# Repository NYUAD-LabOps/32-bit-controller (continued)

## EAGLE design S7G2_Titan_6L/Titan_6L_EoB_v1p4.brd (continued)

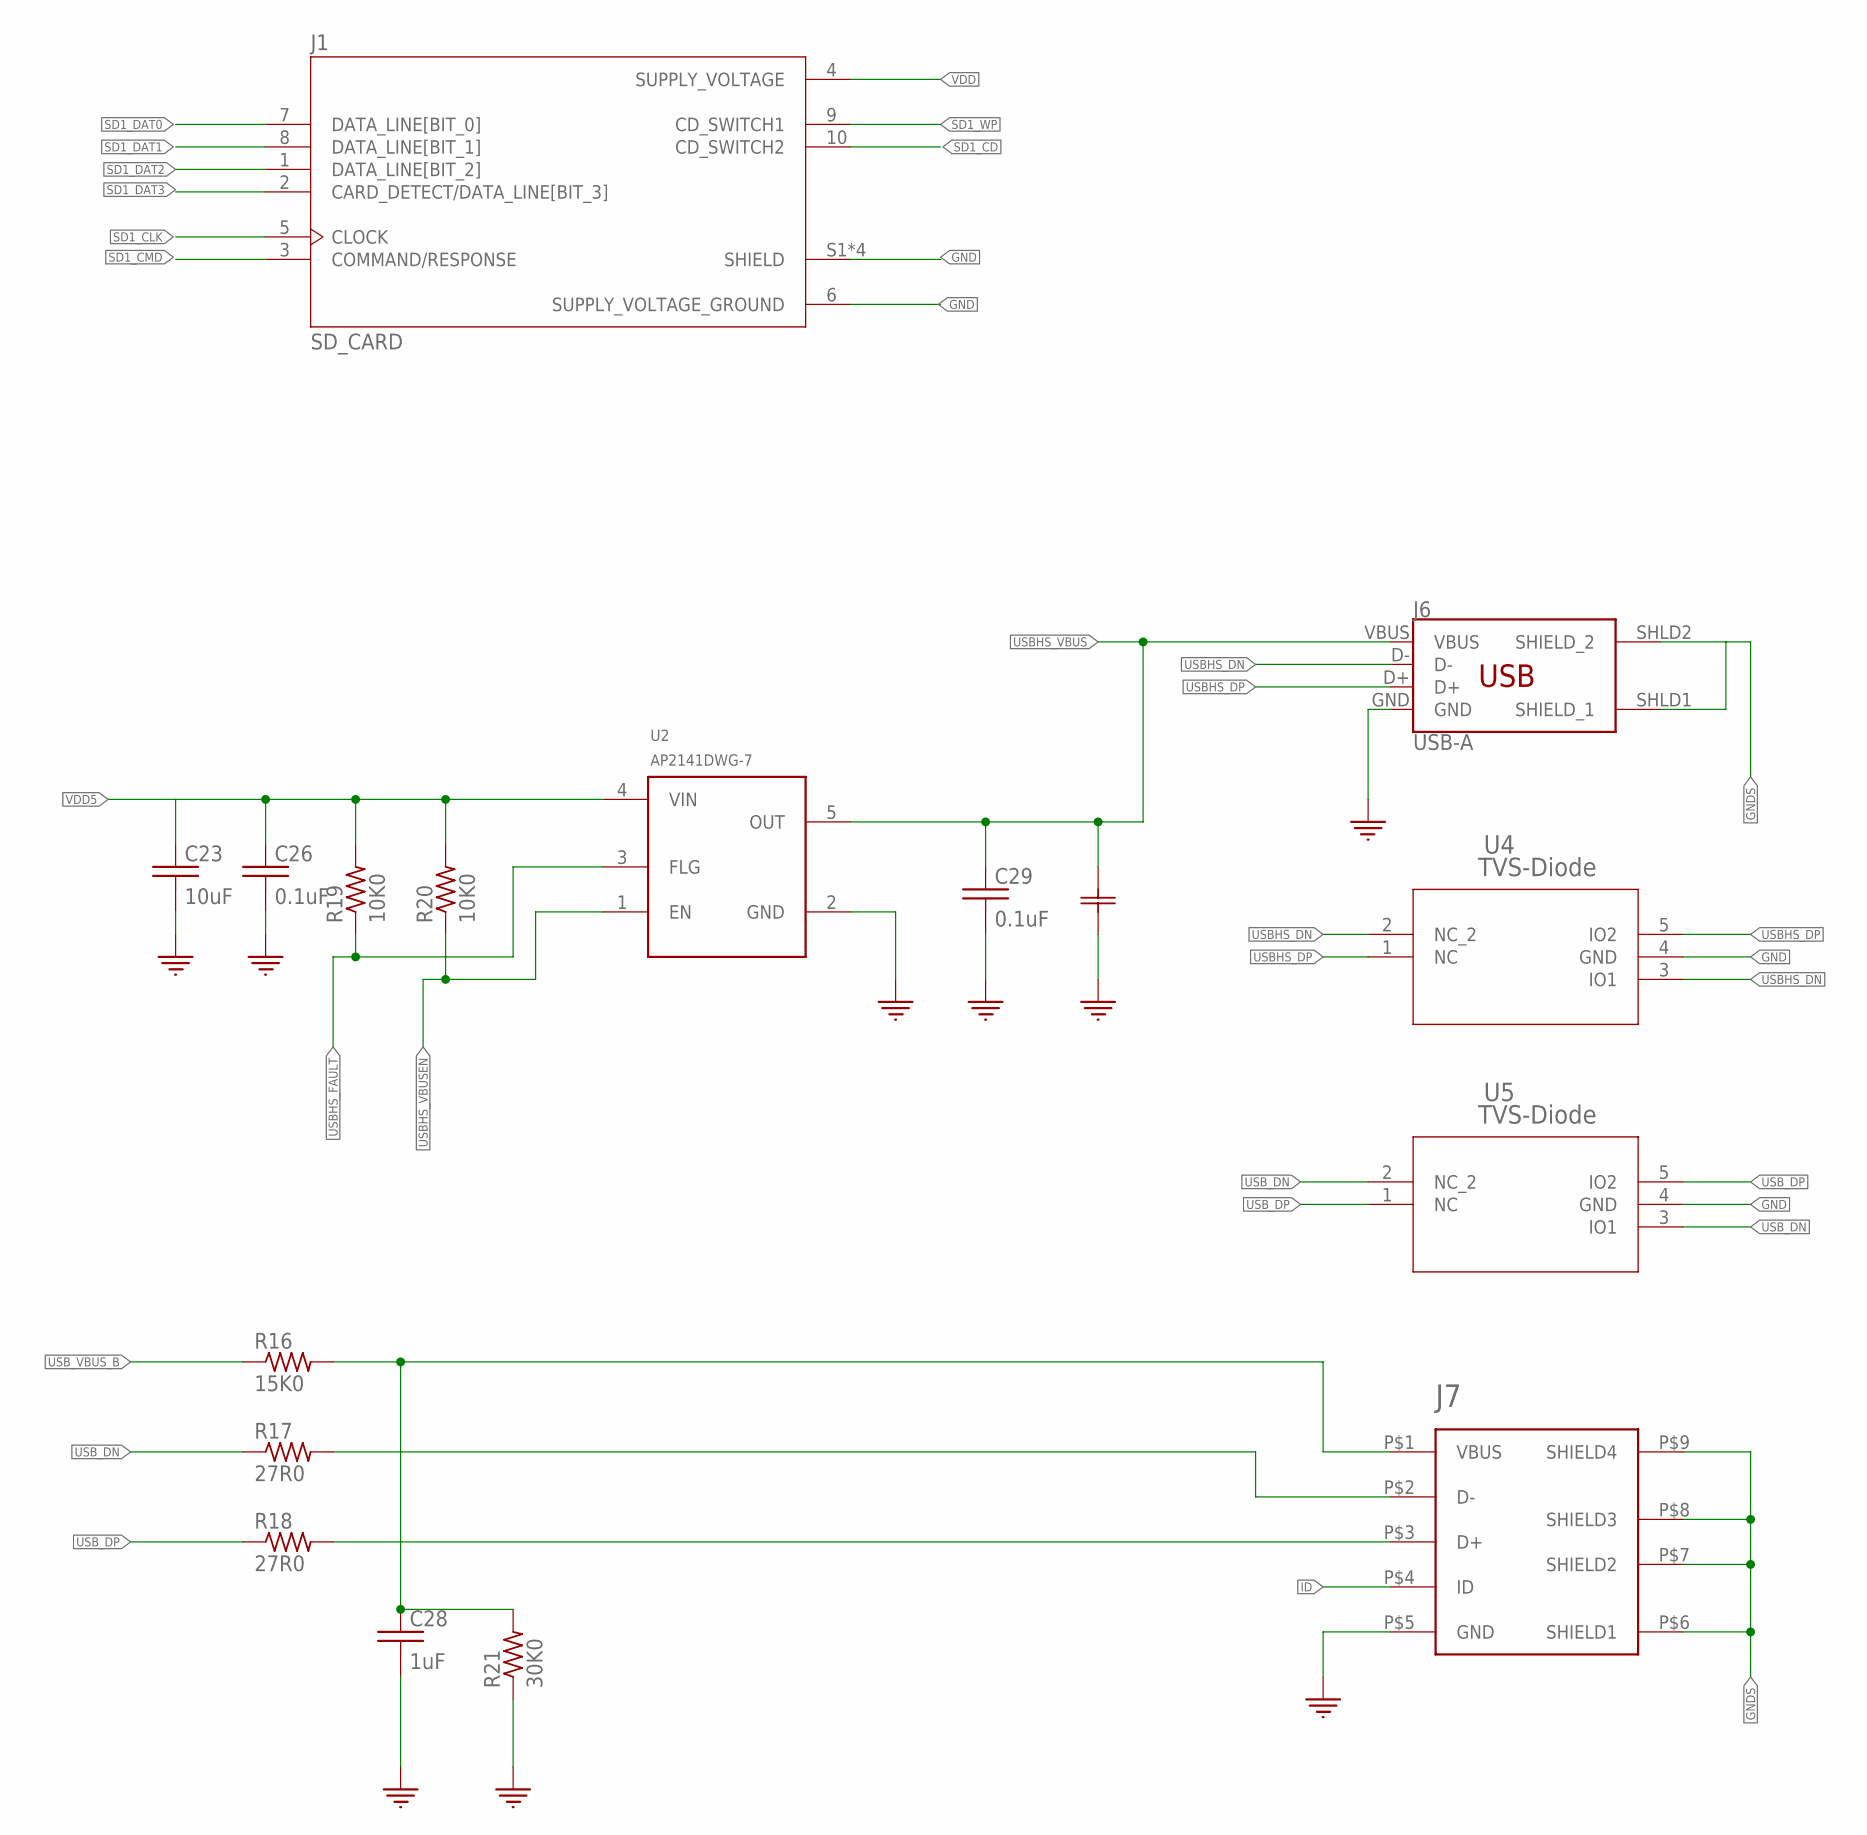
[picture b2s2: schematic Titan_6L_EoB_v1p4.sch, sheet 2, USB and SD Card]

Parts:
C1: TLJT107M010R0900CAP_1210TJLJ_3P5X2P8_DIO-M; CAP_1210TJLJ_3P5X2P8_DIO-M
C23: 10uF; 0402
C26, C29: 0.1uF; 0402
C28: 1uF; 0402
J1: SD_CARD
J6: USB-A; USB_A_SMT
J7: USB-B-Micro; USB_MICRO-B
R16: 15K0; 0402
R17, R18: 27R0; 0402
R19, R20: 10K0; 0402
R21: 30K0; 0402
U2: AP2151DWG-7; SOT-23-5
U4, U5: TVS-Diode; DRL5

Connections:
D+: J7.P$3 (D+), R18.P$2 (2)
D-: J7.P$2 (D-), R17.P$2 (2)
GND: C1.2, C23.P$2 (2), C26.P$2 (2), C28.P$2 (2), C29.P$2 (2), J1.6 (SUPPLY_VOLTAGE_GROUND), J1.S1 (SHIELD), J1.S2 (SHIELD), J1.S3 (SHIELD), J1.S4 (SHIELD), J6.GND, J7.P$5 (GND), R21.P$1 (1), U2.2 (GND), U4.4 (GND), U5.4 (GND); also elsewhere on the board
GNDS: J6.SHLD1 (SHIELD_1), J6.SHLD2 (SHIELD_2), J7.P$6 (SHIELD1), J7.P$7 (SHIELD2), J7.P$8 (SHIELD3), J7.P$9 (SHIELD4); also elsewhere on the board
ID: J7.P$4 (ID)
SD1_CD: J1.10 (CD_SWITCH2); also elsewhere on the board
SD1_CLK: J1.5 (CLOCK); also elsewhere on the board
SD1_CMD: J1.3 (COMMAND/RESPONSE); also elsewhere on the board
SD1_DAT0: J1.7 (DATA_LINE[BIT_0]); also elsewhere on the board
SD1_DAT1: J1.8 (DATA_LINE[BIT_1]); also elsewhere on the board
SD1_DAT2: J1.1 (DATA_LINE[BIT_2]); also elsewhere on the board
SD1_DAT3: J1.2 (CARD_DETECT/DATA_LINE[BIT_3]); also elsewhere on the board
SD1_WP: J1.9 (CD_SWITCH1); also elsewhere on the board
USBHS_DN: J6.D-, U4.2 (NC_2), U4.3 (IO1); also elsewhere on the board
USBHS_DP: J6.D+, U4.1 (NC), U4.5 (IO2); also elsewhere on the board
USBHS_FAULT: R19.P$1 (1), U2.3 (FLG); also elsewhere on the board
USBHS_VBUS: C1.1, C29.P$1 (1), J6.VBUS, U2.5 (OUT); also elsewhere on the board
USBHS_VBUSEN: R20.P$1 (1), U2.1 (EN)
USB_DN: R17.P$1 (1), U5.2 (NC_2), U5.3 (IO1); also elsewhere on the board
USB_DP: R18.P$1 (1), U5.1 (NC), U5.5 (IO2); also elsewhere on the board
USB_VBUS_B: R16.P$1 (1); also elsewhere on the board
VBUS: C28.P$1 (1), J7.P$1 (VBUS), R16.P$2 (2), R21.P$2 (2)
VDD: J1.4 (SUPPLY_VOLTAGE); also elsewhere on the board
VDD5: C23.P$1 (1), C26.P$1 (1), R19.P$2 (2), R20.P$2 (2), U2.4 (VIN); also elsewhere on the board

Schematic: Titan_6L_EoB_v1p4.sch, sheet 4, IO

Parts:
J8, J9, J11, J23, J25, J26, J27, J28, J29, J30, J31, J32, J33, J34: CONN_530470210_PICOBLADE_X_2; CON_530470210_MOL
J10, J13, J14, J15, J16, J17, J18, J19, J20, J21, J22, J24: CONN_530470410_PICOBLADE_X_4; CON_530470410_MOL
J12: 10-pos; 2X5
LED3, LED4, LED5, LED6, LED7, LED8, LED9, LED10, LED11, LED12, LED13, LED14, LED15, LED16: Green; 0805
R1, R2, R96, R97, R102, R103, R105, R106: 100K; 0402
R3, R12, R91, R93: 500R0; 0402
R4, R8, R61, R67, R70, R73, R78, R81, R84, R88: 2.2K; 0402
R6, R9, R11, R27, R62, R68, R71, R76, R79, R82, R85, R89, R92, R95: 470R0; 0402
R7, R10, R63, R69, R72, R77, R80, R83, R86, R90: 10K0; 0402
R28, R29, R30, R31, R32, R33, R34, R35, R36, R37, R38, R39, R40, R41, R42, R43, R44, R45, R46, R47, R48, R49, R50, R51, R52, R53, R54, R55, R56, R57, R58, R59, R60, R64, R65, R66: 33R0; 0402
TH01, TH02, TH03, TH04, TH05, TH06, TH07, TH08: CONN_530470210_PICOBLADE_X_2; CON_530470210_MOL
U7, U8, U9, U10, U11, U12, U13, U14, U15, U16, U17, U18, U19, U20, U21, U22, U23, U24, U25, U26, U27, U28, U29, U30, U31, U32, U33, U34, U35, U36, U37, U38, U39, U40, U41, U42, U43, U44, U45, U46, U47, U48, U49, U50, U51, U52, U53, U54, U55, U56: NPN; SOT323

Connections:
ESTOP: R89.P$2 (2), R90.P$2 (2), U53.2 (E(1)); also elsewhere on the board
GND: J8.1, J9.1, J10.1, J13.1, J14.1, J15.1, J16.1, J17.1, J18.1, J19.1, J20.1, J21.1, J22.1, J23.1, J24.1, J25.1, J26.1, J27.1, J28.1, J29.1, J30.1, J31.1, LED3.2 (C), LED4.2 (C), LED6.2 (C), LED7.2 (C), LED8.2 (C), LED9.2 (C), LED10.2 (C), LED11.2 (C), LED12.2 (C), LED13.2 (C), R7.P$1 (1), R10.P$1 (1), R63.P$1 (1), R69.P$1 (1), R72.P$1 (1), R77.P$1 (1), R80.P$1 (1), R83.P$1 (1), R86.P$1 (1), R90.P$1 (1), TH01.1, TH02.1, TH03.1, TH04.1, TH05.1, TH06.1, TH07.1, TH08.1, U9.2 (E(1)), U10.2 (E(1)), U11.2 (E(1)), U12.2 (E(1)), U13.2 (E(1)), U14.2 (E(1)), U15.2 (E(1)), U16.2 (E(1)), U17.2 (E(1)), U18.2 (E(1)), U19.2 (E(1)), U20.2 (E(1)), U21.2 (E(1)), U22.2 (E(1)), U23.2 (E(1)), U24.2 (E(1)), U25.2 (E(1)), U26.2 (E(1)), U27.2 (E(1)), U28.2 (E(1)), U29.2 (E(1)), U30.2 (E(1)), U31.2 (E(1)), U32.2 (E(1)), U33.2 (E(1)), U34.2 (E(1)), U35.2 (E(1)), U36.2 (E(1)), U37.2 (E(1)), U38.2 (E(1)), U39.2 (E(1)), U40.2 (E(1)), U41.2 (E(1)), U42.2 (E(1)), U45.2 (E(1)), U46.2 (E(1)), U47.2 (E(1)), U54.2 (E(1)), U55.2 (E(1)), U56.2 (E(1)); also elsewhere on the board
LS_01: R6.P$2 (2), R7.P$2 (2), U7.2 (E(1)); also elsewhere on the board
LS_02: R9.P$2 (2), R10.P$2 (2), U8.2 (E(1)); also elsewhere on the board
LS_03: R62.P$2 (2), R63.P$2 (2), U43.2 (E(1)); also elsewhere on the board
LS_04: R68.P$2 (2), R69.P$2 (2), U44.2 (E(1)); also elsewhere on the board
LS_05: R71.P$2 (2), R72.P$2 (2), U48.2 (E(1)); also elsewhere on the board
LS_06: R76.P$2 (2), R77.P$2 (2), U49.2 (E(1)); also elsewhere on the board
LS_07: R79.P$2 (2), R80.P$2 (2), U50.2 (E(1)); also elsewhere on the board
LS_08: R82.P$2 (2), R83.P$2 (2), U51.2 (E(1)); also elsewhere on the board
LS_09: R85.P$2 (2), R86.P$2 (2), U52.2 (E(1)); also elsewhere on the board
LS_RET: J8.2, J9.2, J23.2, J25.2, J26.2, J27.2, J28.2, J29.2, J30.2, J31.2, R4.P$1 (1), R8.P$1 (1), R61.P$1 (1), R67.P$1 (1), R70.P$1 (1), R73.P$1 (1), R78.P$1 (1), R81.P$1 (1), R84.P$1 (1), R88.P$1 (1)
M1_DIR: R29.P$1 (1); also elsewhere on the board
M1_ENABLE: R30.P$1 (1); also elsewhere on the board
M1_STEP: R28.P$1 (1); also elsewhere on the board
M2_DIR: R32.P$1 (1); also elsewhere on the board
M2_ENABLE: R33.P$1 (1); also elsewhere on the board
M2_STEP: R31.P$1 (1); also elsewhere on the board
M3_DIR: R35.P$1 (1); also elsewhere on the board
M3_ENABLE: R36.P$1 (1); also elsewhere on the board
M3_STEP: R34.P$1 (1); also elsewhere on the board
M4_DIR: R38.P$1 (1); also elsewhere on the board
M4_ENABLE: R39.P$1 (1); also elsewhere on the board
M4_STEP: R37.P$1 (1); also elsewhere on the board
M5_DIR: R41.P$1 (1); also elsewhere on the board
M5_ENABLE: R42.P$1 (1); also elsewhere on the board
M5_STEP: R40.P$1 (1); also elsewhere on the board
M6_DIR: R47.P$1 (1); also elsewhere on the board
M6_ENABLE: R48.P$1 (1); also elsewhere on the board
M6_STEP: R46.P$1 (1); also elsewhere on the board
M7_DIR: R53.P$1 (1); also elsewhere on the board
M7_ENABLE: R54.P$1 (1); also elsewhere on the board
M7_STEP: R52.P$1 (1); also elsewhere on the board
M8_DIR: R59.P$1 (1); also elsewhere on the board
M8_ENABLE: R60.P$1 (1); also elsewhere on the board
M8_STEP: R58.P$1 (1); also elsewhere on the board
M9_DIR: R44.P$1 (1); also elsewhere on the board
M9_ENABLE: R45.P$1 (1); also elsewhere on the board
M9_STEP: R43.P$1 (1); also elsewhere on the board
M10_DIR: R56.P$1 (1); also elsewhere on the board
M10_ENABLE: R57.P$1 (1); also elsewhere on the board
M10_STEP: R55.P$1 (1); also elsewhere on the board
M11_DIR: R65.P$1 (1); also elsewhere on the board
M11_ENABLE: R66.P$1 (1); also elsewhere on the board
M11_STEP: R64.P$1 (1); also elsewhere on the board
M12_DIR: R50.P$1 (1); also elsewhere on the board
M12_ENABLE: R51.P$1 (1); also elsewhere on the board
M12_STEP: R49.P$1 (1); also elsewhere on the board
MO_DIR: J10.3, J13.3, J14.3, J15.3, J16.3, J17.3, J18.3, J19.3, J20.3, J21.3, J22.3, J24.3, U10.3 (C(3)), U13.3 (C(3)), U16.3 (C(3)), U19.3 (C(3)), U22.3 (C(3)), U25.3 (C(3)), U28.3 (C(3)), U31.3 (C(3)), U34.3 (C(3)), U37.3 (C(3)), U40.3 (C(3)), U46.3 (C(3))
MO_ENABLE: J10.2, J13.2, J14.2, J15.2, J16.2, J17.2, J18.2, J19.2, J20.2, J21.2, J22.2, J24.2, U11.3 (C(3)), U14.3 (C(3)), U17.3 (C(3)), U20.3 (C(3)), U23.3 (C(3)), U26.3 (C(3)), U29.3 (C(3)), U32.3 (C(3)), U35.3 (C(3)), U38.3 (C(3)), U41.3 (C(3)), U47.3 (C(3))
MO_STEP: J10.4, J13.4, J14.4, J15.4, J16.4, J17.4, J18.4, J19.4, J20.4, J21.4, J22.4, J24.4, U9.3 (C(3)), U12.3 (C(3)), U15.3 (C(3)), U18.3 (C(3)), U21.3 (C(3)), U24.3 (C(3)), U27.3 (C(3)), U30.3 (C(3)), U33.3 (C(3)), U36.3 (C(3)), U39.3 (C(3)), U45.3 (C(3))
unnamed: R4.P$2 (2), U7.1 (B(2))
unnamed: LED3.1 (A), R6.P$1 (1)
unnamed: R29.P$2 (2), U10.1 (B(2))
unnamed: R30.P$2 (2), U11.1 (B(2))
unnamed: R28.P$2 (2), U9.1 (B(2))
unnamed: R32.P$2 (2), U13.1 (B(2))
unnamed: R33.P$2 (2), U14.1 (B(2))
unnamed: R31.P$2 (2), U12.1 (B(2))
unnamed: R35.P$2 (2), U16.1 (B(2))
unnamed: R36.P$2 (2), U17.1 (B(2))
unnamed: R34.P$2 (2), U15.1 (B(2))
unnamed: R38.P$2 (2), U19.1 (B(2))
unnamed: R39.P$2 (2), U20.1 (B(2))
unnamed: R37.P$2 (2), U18.1 (B(2))
unnamed: R41.P$2 (2), U22.1 (B(2))
unnamed: R42.P$2 (2), U23.1 (B(2))
unnamed: R40.P$2 (2), U21.1 (B(2))
unnamed: R44.P$2 (2), U25.1 (B(2))
unnamed: R45.P$2 (2), U26.1 (B(2))
unnamed: R43.P$2 (2), U24.1 (B(2))
unnamed: R47.P$2 (2), U28.1 (B(2))
unnamed: R48.P$2 (2), U29.1 (B(2))
unnamed: R46.P$2 (2), U27.1 (B(2))
unnamed: R50.P$2 (2), U31.1 (B(2))
unnamed: R51.P$2 (2), U32.1 (B(2))
unnamed: R49.P$2 (2), U30.1 (B(2))
unnamed: R53.P$2 (2), U34.1 (B(2))
unnamed: R54.P$2 (2), U35.1 (B(2))
unnamed: R52.P$2 (2), U33.1 (B(2))
unnamed: R56.P$2 (2), U37.1 (B(2))
unnamed: R57.P$2 (2), U38.1 (B(2))
unnamed: R55.P$2 (2), U36.1 (B(2))
unnamed: R59.P$2 (2), U40.1 (B(2))
unnamed: R60.P$2 (2), U41.1 (B(2))
unnamed: R58.P$2 (2), U39.1 (B(2))
unnamed: R8.P$2 (2), U8.1 (B(2))
unnamed: LED4.1 (A), R9.P$1 (1)
unnamed: R65.P$2 (2), U46.1 (B(2))
unnamed: R66.P$2 (2), U47.1 (B(2))
unnamed: R64.P$2 (2), U45.1 (B(2))
unnamed: R3.P$2 (2), U42.1 (B(2))
unnamed: R61.P$2 (2), U43.1 (B(2))
unnamed: LED6.1 (A), R62.P$1 (1)
unnamed: R67.P$2 (2), U44.1 (B(2))
unnamed: LED7.1 (A), R68.P$1 (1)
unnamed: R70.P$2 (2), U48.1 (B(2))
unnamed: LED8.1 (A), R71.P$1 (1)
unnamed: R73.P$2 (2), U49.1 (B(2))
unnamed: LED9.1 (A), R76.P$1 (1)
unnamed: R78.P$2 (2), U50.1 (B(2))
unnamed: LED10.1 (A), R79.P$1 (1)
unnamed: R81.P$2 (2), U51.1 (B(2))
unnamed: LED11.1 (A), R82.P$1 (1)
unnamed: R84.P$2 (2), U52.1 (B(2))
unnamed: LED12.1 (A), R85.P$1 (1)
unnamed: R88.P$2 (2), U53.1 (B(2))
unnamed: LED13.1 (A), R89.P$1 (1)
unnamed: J11.2, LED5.2 (C), U42.3 (C(3))
unnamed: LED5.1 (A), R11.P$1 (1)
unnamed: R12.P$2 (2), U54.1 (B(2))
unnamed: J32.2, LED14.2 (C), U54.3 (C(3))
unnamed: LED14.1 (A), R27.P$1 (1)
unnamed: R91.P$2 (2), U55.1 (B(2))
unnamed: J33.2, LED15.2 (C), U55.3 (C(3))
unnamed: LED15.1 (A), R92.P$1 (1)
unnamed: R93.P$2 (2), U56.1 (B(2))
unnamed: J34.2, LED16.2 (C), U56.3 (C(3))
unnamed: LED16.1 (A), R95.P$1 (1)
P0_02_TH_01: R1.P$1 (1), TH01.2; also elsewhere on the board
P0_04_TH_02: R2.P$1 (1), TH02.2; also elsewhere on the board
P0_05_TH_03: R102.P$1 (1), TH03.2; also elsewhere on the board
P0_06_TH_04: R103.P$1 (1), TH04.2; also elsewhere on the board
P0_08_TH_05: R105.P$1 (1), TH05.2; also elsewhere on the board
P0_09_TH_06: R106.P$1 (1), TH06.2; also elsewhere on the board
P0_14_TH_07: R96.P$1 (1), TH07.2; also elsewhere on the board
P0_15_TH_08: R97.P$1 (1), TH08.2; also elsewhere on the board
P3_10: J12.1; also elsewhere on the board
P3_11: J12.2; also elsewhere on the board
P3_12: J12.3; also elsewhere on the board
P3_15: J12.10; also elsewhere on the board
P9_00: J12.9; also elsewhere on the board
P9_01: J12.8; also elsewhere on the board
P9_05: J12.4; also elsewhere on the board
P9_06: J12.5; also elsewhere on the board
P9_07: J12.6; also elsewhere on the board
P9_08: J12.7; also elsewhere on the board
RELAY_01: R93.P$1 (1); also elsewhere on the board
RELAY_02: R91.P$1 (1); also elsewhere on the board
RELAY_03: R12.P$1 (1); also elsewhere on the board
RELAY_04: R3.P$1 (1); also elsewhere on the board
VDD: R1.P$2 (2), R2.P$2 (2), R96.P$2 (2), R97.P$2 (2), R102.P$2 (2), R103.P$2 (2), R105.P$2 (2), R106.P$2 (2), U7.3 (C(3)), U8.3 (C(3)), U43.3 (C(3)), U44.3 (C(3)), U48.3 (C(3)), U49.3 (C(3)), U50.3 (C(3)), U51.3 (C(3)), U52.3 (C(3)), U53.3 (C(3)); also elsewhere on the board
VDD5: J11.1, J32.1, J33.1, J34.1, R11.P$2 (2), R27.P$2 (2), R92.P$2 (2), R95.P$2 (2); also elsewhere on the board

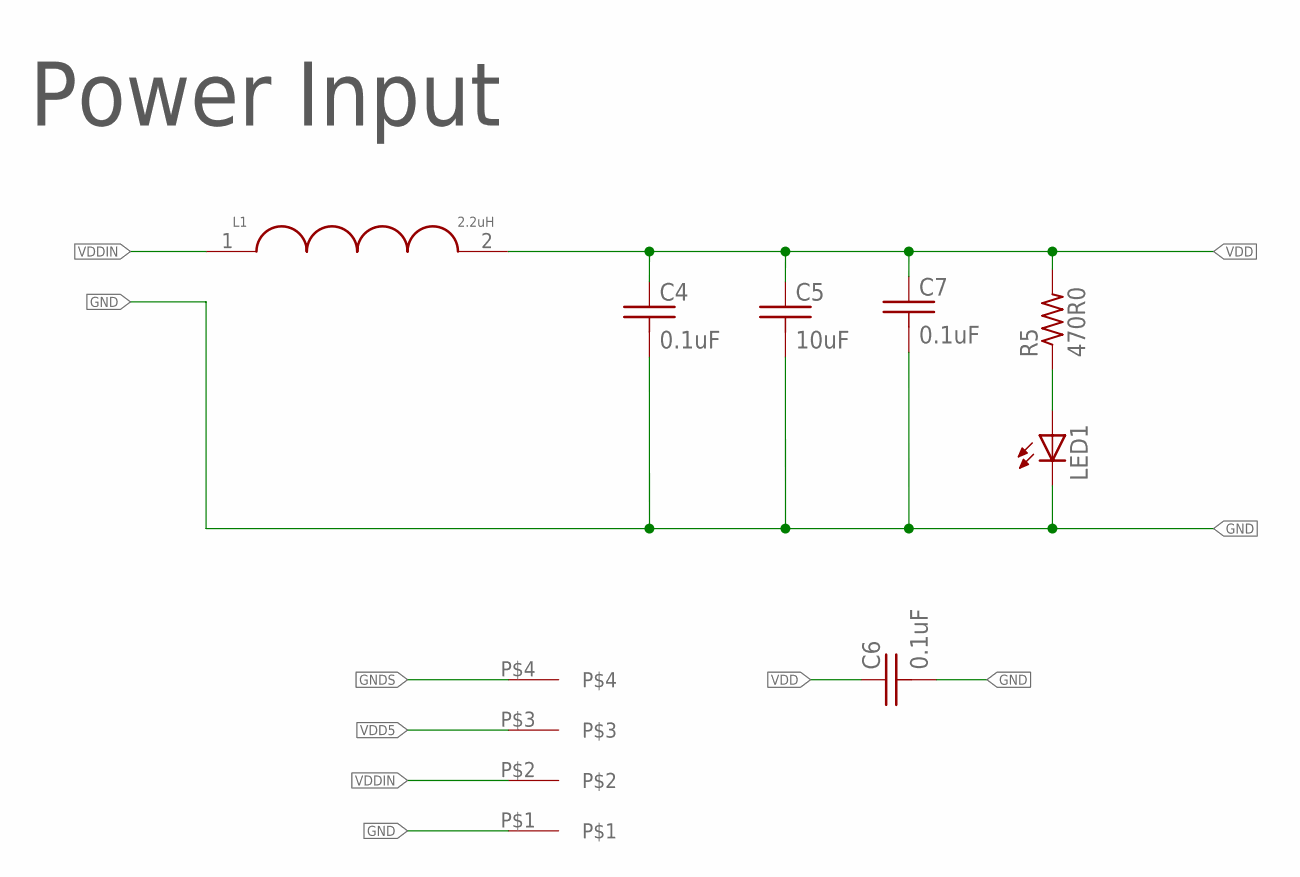
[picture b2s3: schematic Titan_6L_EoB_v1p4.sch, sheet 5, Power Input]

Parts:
C4, C6, C7: 0.1uF; 0402
C5: 10uF; 0402
J2: 4-pos; 1X4_3.81MM_PITCH
L1: 2.2uH; 1008
LED1: Green; 0805
R5: 470R0; 0402

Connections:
GND: C4.P$2 (2), C5.P$2 (2), C6.P$2 (2), C7.P$2 (2), J2.P$1, LED1.2 (C); also elsewhere on the board
GNDS: J2.P$4; also elsewhere on the board
unnamed: LED1.1 (A), R5.P$1 (1)
VDD: C4.P$1 (1), C5.P$1 (1), C6.P$1 (1), C7.P$1 (1), L1.2, R5.P$2 (2); also elsewhere on the board
VDD5: J2.P$3; also elsewhere on the board
VDDIN: J2.P$2, L1.1

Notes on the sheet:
Power Input

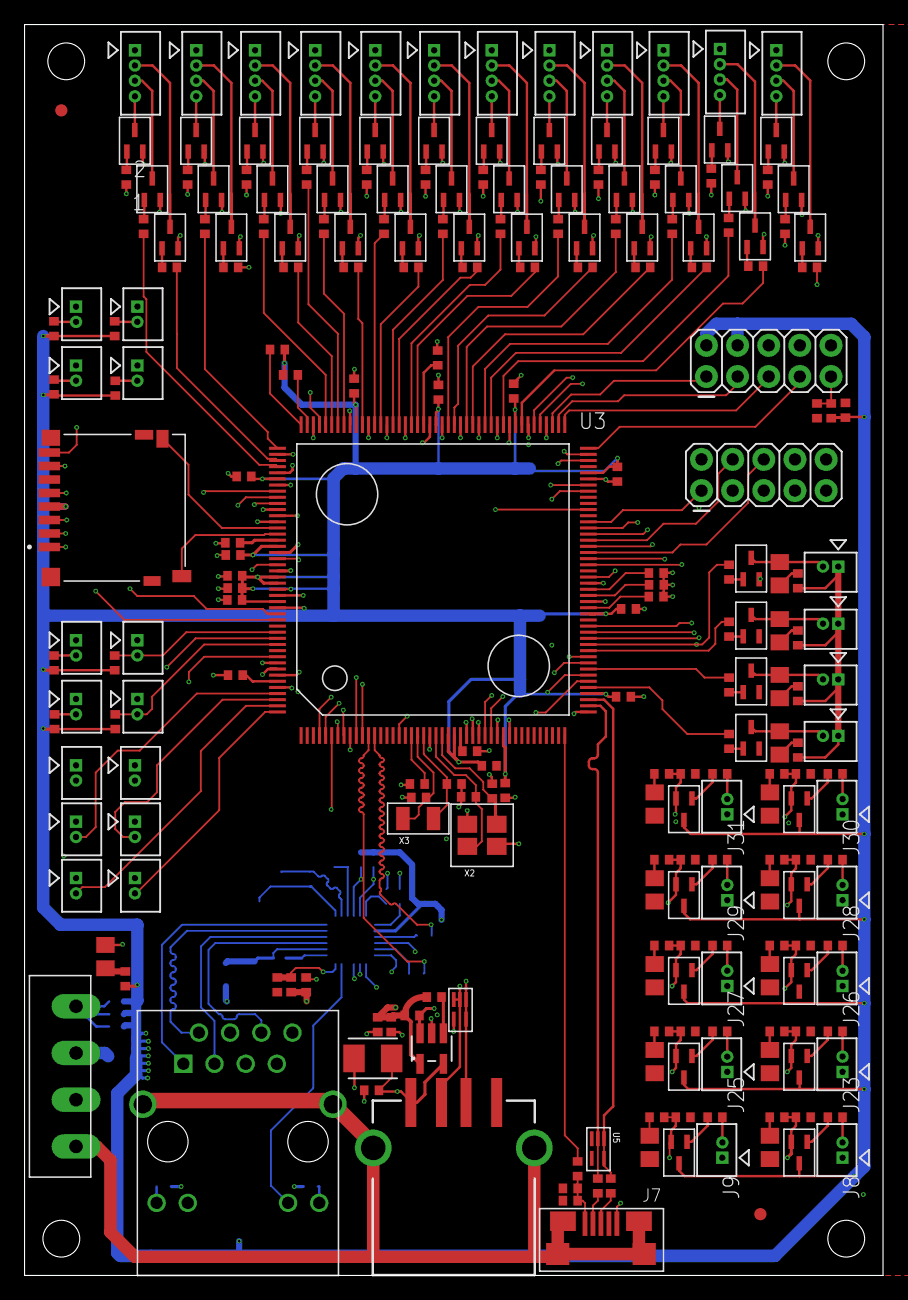
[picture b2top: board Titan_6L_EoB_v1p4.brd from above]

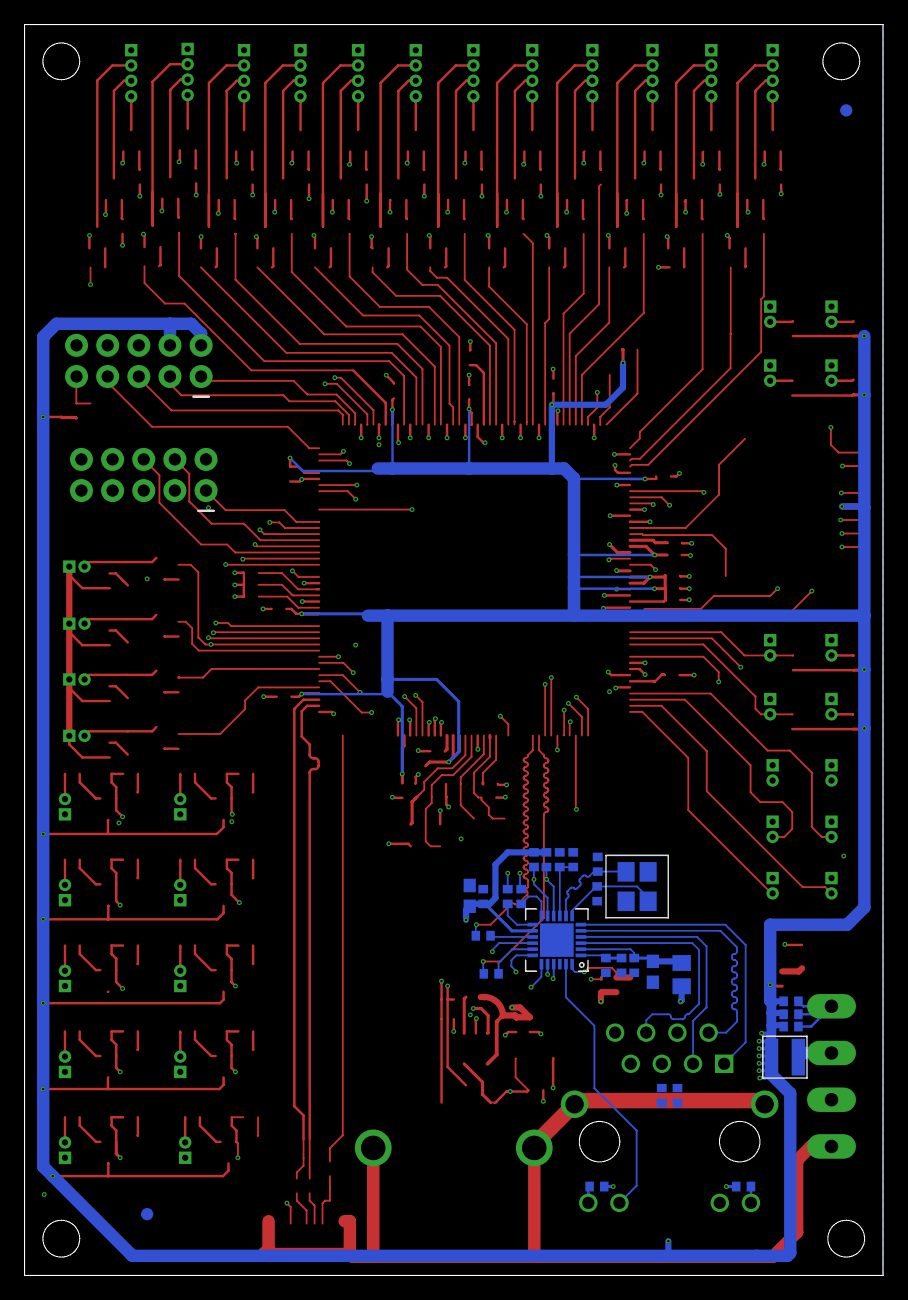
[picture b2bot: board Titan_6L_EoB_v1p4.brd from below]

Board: 6 copper layers, 70.0 x 102.0 mm, 276 parts (29 on the bottom side), 219 nets.

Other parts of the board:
C15, C31, C47, C52: 0.1uF; 0402
C44, C45: 24pF; 0402
C46, C51: 22uF; 0603
C48: 2.2uF; 0402
C49: .1uF; 0402
C50: 100pF; 0402
FB2/2: 0805
R107, R108: 470; 0402
R109: 6k49; 0402
R110, R111: 10K; 0402
R112, R113: 1K50; 0402
R114, R115, R116, R117: 33; 0402
U6: KSZ8081RNACAQFN-24-M; QFN-24-M
U$2: RJ45_TH_ELEC
U$3: SMD_3225
U$4: 10uF; 0402

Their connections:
C58: C15.P$1, U$2.4
C60: C31.P$1, U$2.5
CRS_DV: R117.P$2, U6.15
ETH_CLK: U6.16; also elsewhere on the board
ETH_CRS_DV: R117.P$1; also elsewhere on the board
ETH_IRQ14: R110.P$1, U6.18; also elsewhere on the board
ETH_MDC: R112.P$1, U6.11; also elsewhere on the board
ETH_MDIO: R113.P$1, U6.10; also elsewhere on the board
ETH_RESET: R111.P$1, U6.24, U$4.P$1; also elsewhere on the board
ETH_RXD0: R115.P$1; also elsewhere on the board
ETH_RXD1: R114.P$1; also elsewhere on the board
ETH_RX_ER: R116.P$1; also elsewhere on the board
ETH_TXD0: U6.20; also elsewhere on the board
ETH_TXD1: U6.21; also elsewhere on the board
ETH_TXD_EN: U6.19; also elsewhere on the board
GND: C15.P$2, C31.P$2, C44.P$2, C45.P$2, C46.2, C47.P$2, C48.P$2, C49.P$2, C50.P$2, C51.2, C52.P$2, R109.P$1, U6.22, U6.25, U$2.8, U$2.10, U$3.2, U$3.4, U$4.P$2; also elsewhere on the board
GNDS: U$2.13, U$2.14; also elsewhere on the board
LED1/SPEED: U6.23, U$2.11
R51: R107.P$1, U$2.12
R52: R108.P$1, U$2.9
REXT: C50.P$1, R109.P$2, U6.9
RXD0: R115.P$2, U6.13
RXD1: R114.P$2, U6.12
RXER: R116.P$2, U6.17
RXM: U6.3, U$2.6
RXP: U6.4, U$2.3
TXM: U6.5, U$2.2
TXP: U6.6, U$2.1
VDD: C51.1, C52.P$1, FB2/2.1, R107.P$2, R108.P$2, R110.P$2, R111.P$2, R112.P$2, R113.P$2, U6.14; also elsewhere on the board
VDD_1.2: C48.P$1, C49.P$1, U6.1
VDD_ENET1: C46.1, C47.P$1, FB2/2.2, U6.2
XII: C45.P$1, U6.8, U$3.1
XOO: C44.P$1, U6.7, U$3.3
